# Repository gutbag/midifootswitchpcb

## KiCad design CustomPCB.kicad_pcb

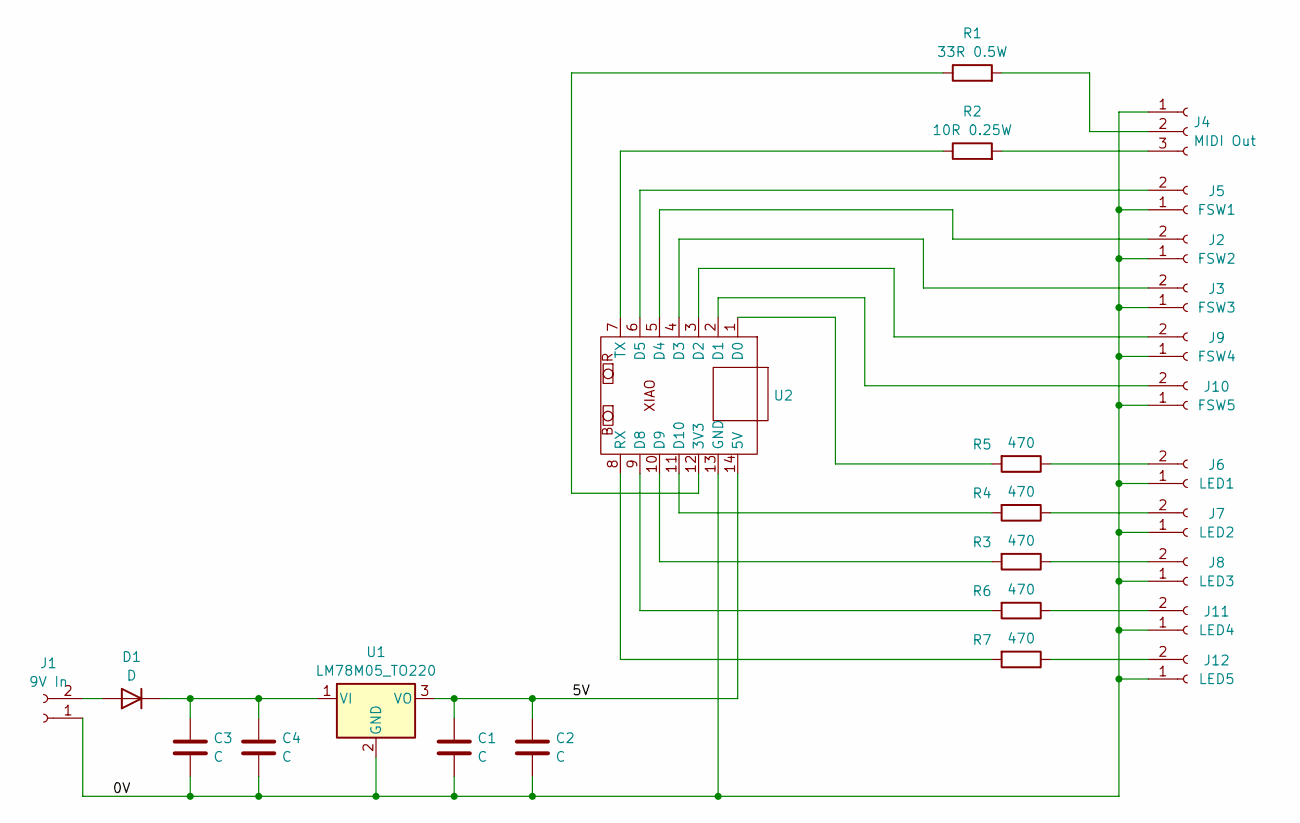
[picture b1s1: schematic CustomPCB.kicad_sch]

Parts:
C1, C3: C; CP_Radial_D4.0mm_P1.50mm
C2, C4: C; C_Disc_D4.3mm_W1.9mm_P5.00mm
D1: D; D_A-405_P10.16mm_Horizontal
J1: 9V In; PinHeader_1x02_P2.54mm_Vertical
J2: FSW2; PinHeader_1x02_P2.54mm_Vertical
J3: FSW3; PinHeader_1x02_P2.54mm_Vertical
J4: MIDI Out; PinHeader_1x03_P2.54mm_Vertical
J5: FSW1; PinHeader_1x02_P2.54mm_Vertical
J6: LED1; PinHeader_1x02_P2.54mm_Vertical
J7: LED2; PinHeader_1x02_P2.54mm_Vertical
J8: LED3; PinHeader_1x02_P2.54mm_Vertical
J9: FSW4; PinHeader_1x02_P2.54mm_Vertical
J10: FSW5; PinHeader_1x02_P2.54mm_Vertical
J11: LED4; PinHeader_1x02_P2.54mm_Vertical
J12: LED5; PinHeader_1x02_P2.54mm_Vertical
R1: 33R 0.5W; R_Axial_DIN0207_L6.3mm_D2.5mm_P10.16mm_Horizontal
R2: 10R 0.25W; R_Axial_DIN0207_L6.3mm_D2.5mm_P10.16mm_Horizontal
R3, R4, R5, R6, R7: 470; R_Axial_DIN0207_L6.3mm_D2.5mm_P10.16mm_Horizontal
U1: LM78M05_TO220; TO-220-3_Vertical
U2: XIAO

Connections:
/0V: C1.2, C2.2, C3.2, C4.2, J1.1, J2.1, J3.1, J4.1, J5.1, J6.1, J7.1, J8.1, J9.1, J10.1, J11.1, J12.1, U1.2 (GND), U2.13 (GND)
/5V: C1.1, C2.1, U1.3 (VO), U2.14 (5V)
unnamed: D1.2 (A), J1.2
unnamed: C3.1, C4.1, D1.1 (K), U1.1 (VI)
unnamed: J2.2, U2.5 (D4)
unnamed: J3.2, U2.4 (D3)
unnamed: J4.2, R1.2
unnamed: J4.3, R2.2
unnamed: J5.2, U2.6 (D5)
unnamed: J6.2, R5.1
unnamed: J7.2, R4.1
unnamed: J8.2, R3.1
unnamed: J9.2, U2.3 (D2)
unnamed: J10.2, U2.2 (D1)
unnamed: J11.2, R6.1
unnamed: J12.2, R7.1
unnamed: R1.1, U2.12 (3V3)
unnamed: R5.2, U2.1 (D0)
unnamed: R6.2, U2.9 (D8)
unnamed: R3.2, U2.10 (D9)
unnamed: R4.2, U2.11 (D10)
unnamed: R7.2, U2.8 (RX)
unnamed: R2.1, U2.7 (TX)

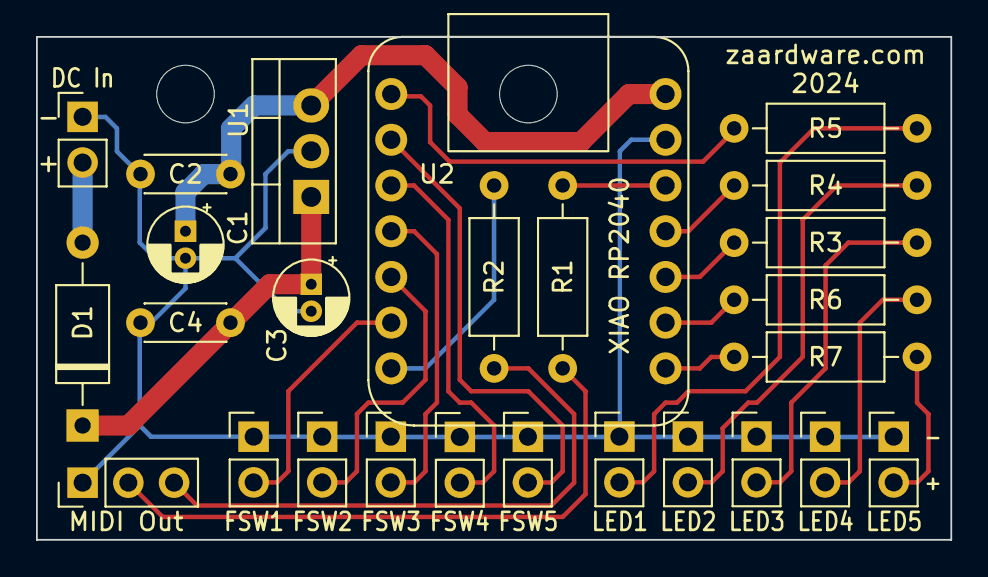
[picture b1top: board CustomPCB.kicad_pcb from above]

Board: 2 copper layers, 50.8 x 27.9 mm, 26 parts (0 on the bottom side), 23 nets.
